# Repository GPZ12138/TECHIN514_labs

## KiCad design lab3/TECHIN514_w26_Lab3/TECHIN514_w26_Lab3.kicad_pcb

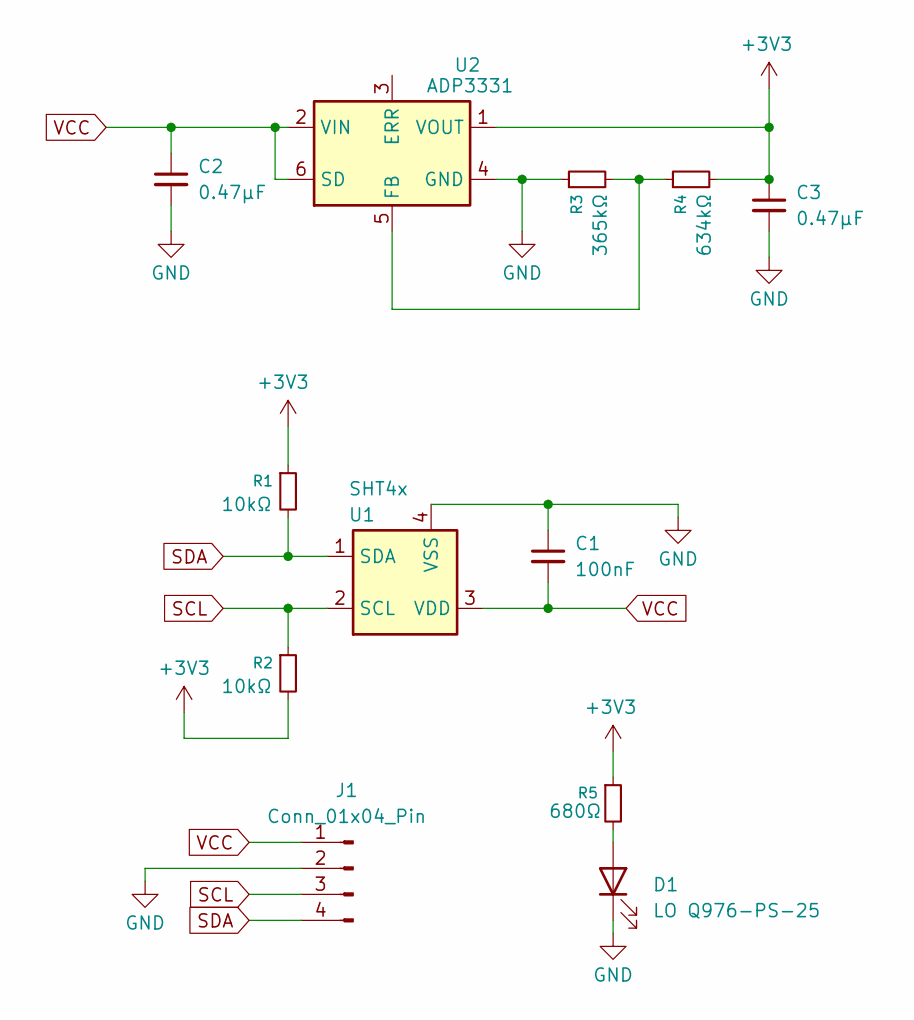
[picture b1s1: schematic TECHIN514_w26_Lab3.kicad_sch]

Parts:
C1: 100nF; C_0603_1608Metric_Pad1.08x0.95mm_HandSolder
C2, C3: 0.47μF; C_0603_1608Metric_Pad1.08x0.95mm_HandSolder
D1: LO Q976-PS-25; LED_0603_1608Metric_Pad1.05x0.95mm_HandSolder
J1: Conn_01x04_Pin; PinHeader_1x04_P2.54mm_Vertical
R1, R2: 10kΩ; R_0603_1608Metric_Pad0.98x0.95mm_HandSolder
R3: 365kΩ; R_0603_1608Metric_Pad0.98x0.95mm_HandSolder
R4: 634kΩ; R_0603_1608Metric_Pad0.98x0.95mm_HandSolder
R5: 680Ω; R_0603_1608Metric_Pad0.98x0.95mm_HandSolder
U1: SHT4x; Sensirion_DFN-4_1.5x1.5mm_P0.8mm_SHT4x_NoCentralPad
U2: ADP3331; SOT-23-6

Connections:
+3V3: C3.1, R1.1, R2.2, R4.2, R5.1, U2.1 (VOUT)
GND: C1.1, C2.2, C3.2, D1.1 (K), J1.2, R3.1, U1.4 (VSS), U2.4 (GND)
unnamed: D1.2 (A), R5.2
unnamed: R3.2, R4.1, U2.5 (FB)
SCL: J1.3, R2.1, U1.2 (SCL)
SDA: J1.4, R1.2, U1.1 (SDA)
VCC: C1.2, C2.1, J1.1, U1.3 (VDD), U2.2 (VIN), U2.6 (SD)

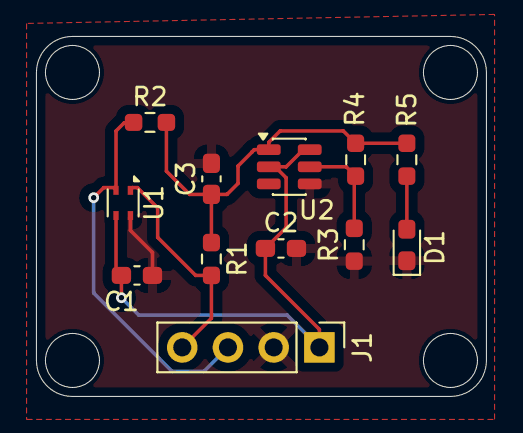
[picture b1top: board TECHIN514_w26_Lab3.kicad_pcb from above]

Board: 2 copper layers, 25.0 x 20.0 mm, 12 parts (0 on the bottom side), 7 nets.

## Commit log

2026-01-13 revise
2026-01-20 week2
2026-01-26 0126
2026-01-26 0126-new
2026-01-26 0126-new2
2026-01-26 lab4
2026-01-26 lab4-ok
2026-01-27 lab3 pcb lab
2026-01-27 lab3 pcb lab-finish
